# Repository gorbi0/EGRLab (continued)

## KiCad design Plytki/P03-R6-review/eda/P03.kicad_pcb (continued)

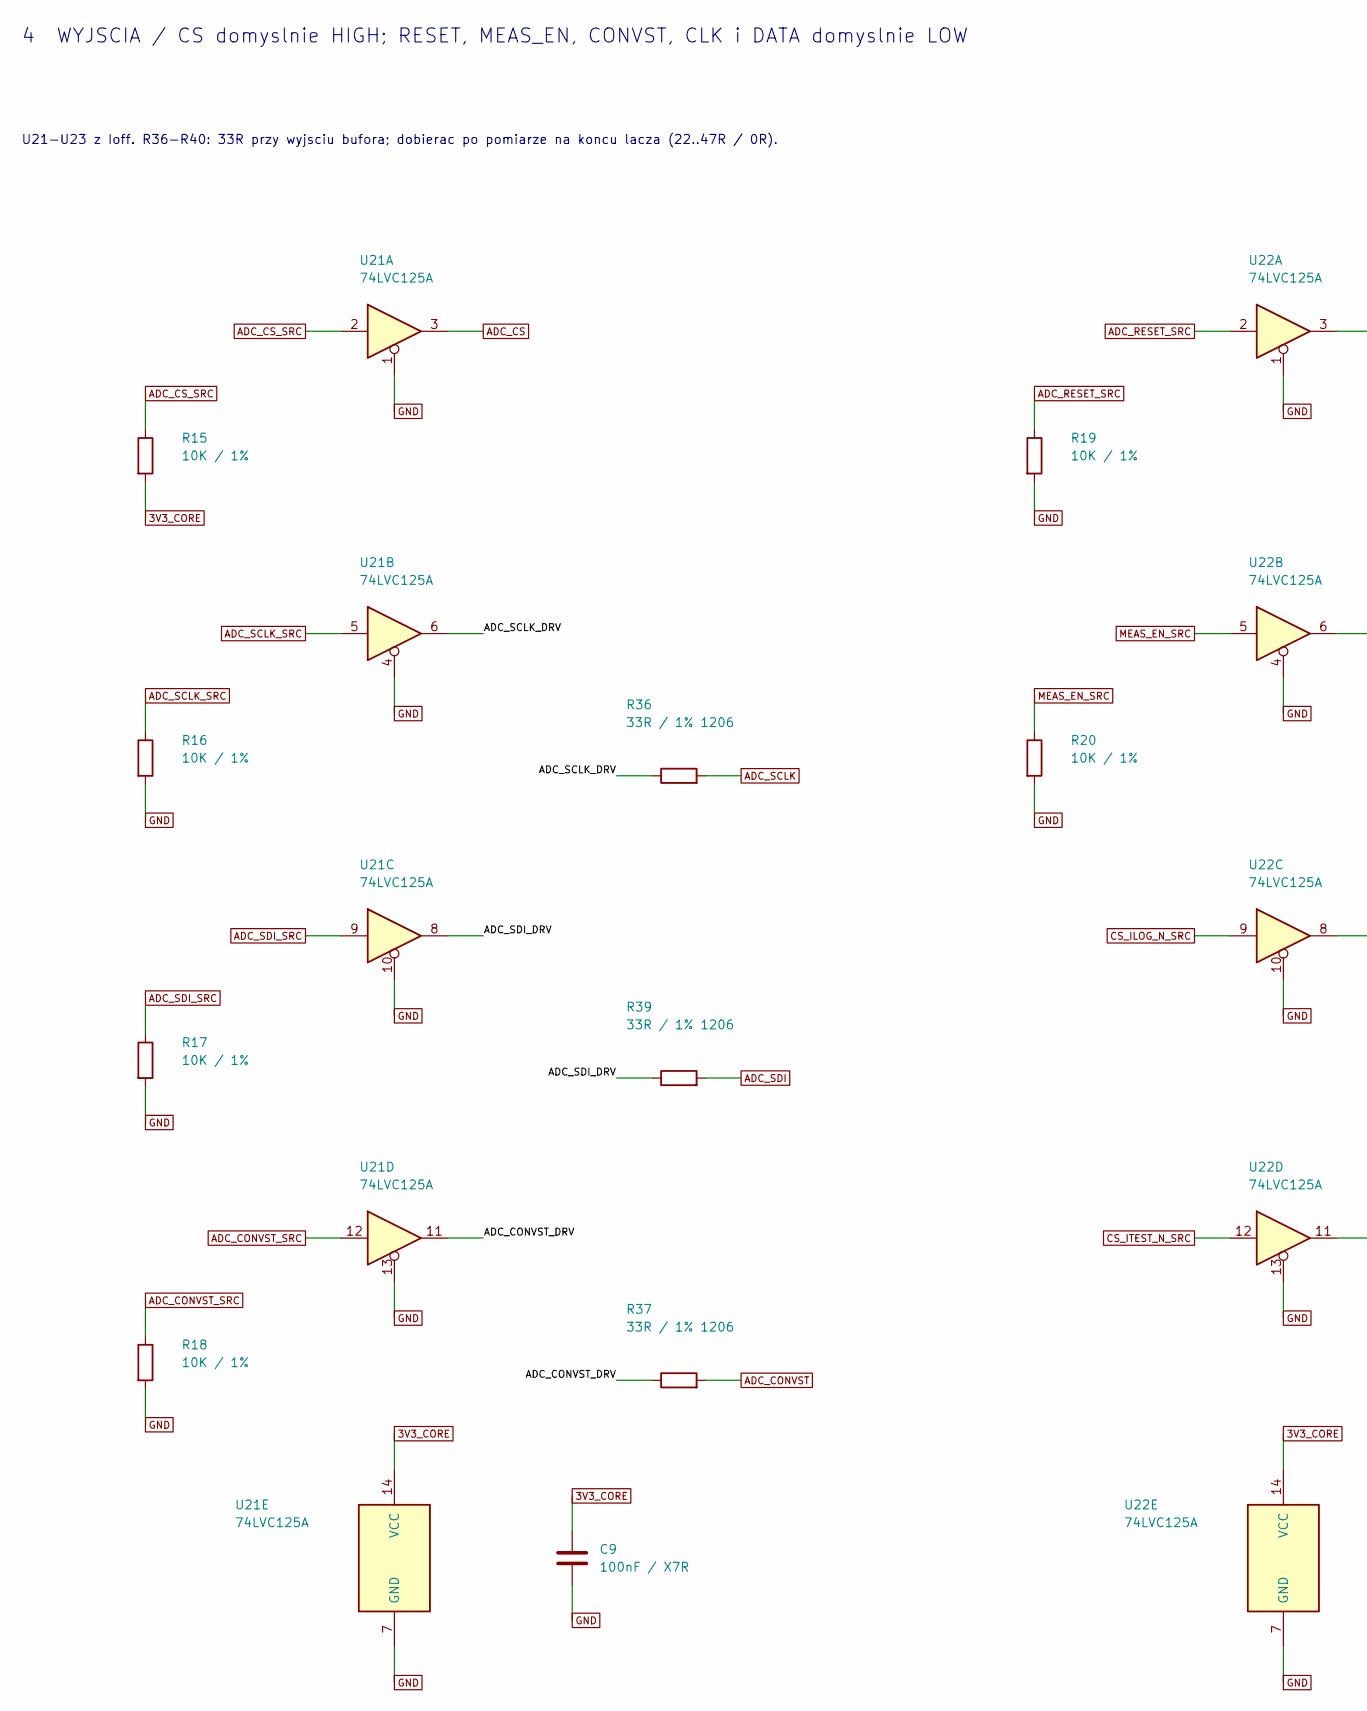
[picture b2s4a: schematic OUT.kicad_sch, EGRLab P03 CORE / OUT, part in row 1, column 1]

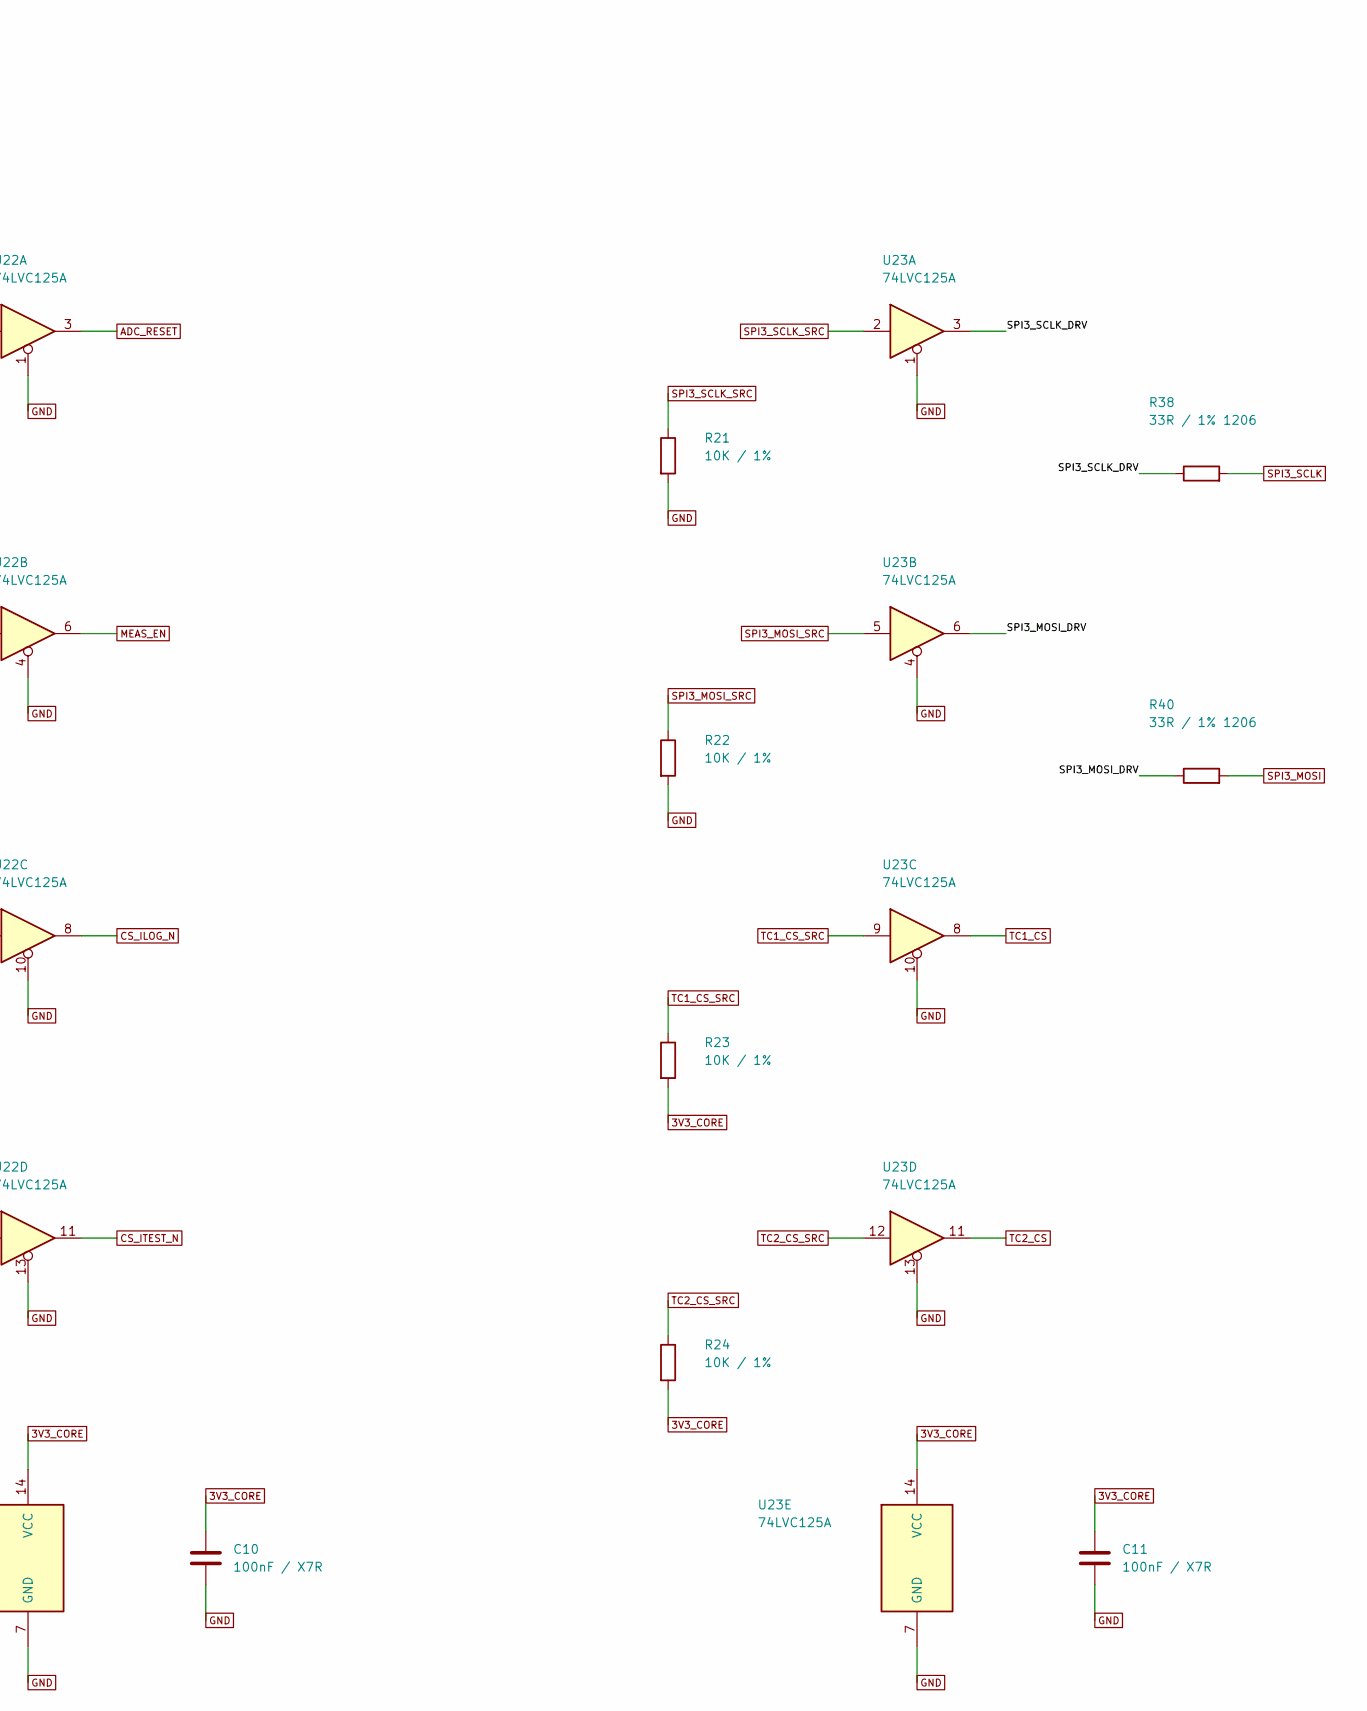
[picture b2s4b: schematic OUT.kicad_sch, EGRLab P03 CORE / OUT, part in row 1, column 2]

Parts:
C9, C10, C11: 100nF / X7R; C_Vishay_K15_H5_P5; MPN K104K15X7RF5TH5
R15, R16, R17, R18, R19, R20, R21, R22, R23, R24: 10K / 1%; R_Axial_DIN0207_L6.3mm_D2.5mm_P5.08mm_Vertical; MPN MF0207FTE-10K
R36, R37, R38, R39, R40: 33R / 1% 1206; R_1206_3216Metric_Pad1.30x1.75mm_HandSolder; MPN RC1206FR-0733RL
U21, U22, U23: 74LVC125A; SOIC-14_3.9x8.7mm_P1.27mm; MPN 74LVC125AD,118 (Nexperia)

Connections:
3V3_CORE: C9.1, C10.1, C11.1, R15.2, R23.2, R24.2, U21.14 (VCC), U22.14 (VCC), U23.14 (VCC); also elsewhere on the board
/OUT/ADC_CONVST_DRV: R37.1, U21.11
/OUT/ADC_SCLK_DRV: R36.1, U21.6
/OUT/ADC_SDI_DRV: R39.1, U21.8
/OUT/SPI3_MOSI_DRV: R40.1, U23.6
/OUT/SPI3_SCLK_DRV: R38.1, U23.3
ADC_CONVST: R37.2; also elsewhere on the board
ADC_CONVST_SRC: R18.1, U21.12; also elsewhere on the board
ADC_CS: U21.3; also elsewhere on the board
ADC_CS_SRC: R15.1, U21.2; also elsewhere on the board
ADC_RESET_SRC: R19.1, U22.2; also elsewhere on the board
ADC_SCLK: R36.2; also elsewhere on the board
ADC_SCLK_SRC: R16.1, U21.5; also elsewhere on the board
ADC_SDI: R39.2; also elsewhere on the board
ADC_SDI_SRC: R17.1, U21.9; also elsewhere on the board
CS_ILOG_N: U22.8; also elsewhere on the board
CS_ILOG_N_SRC: U22.9; also elsewhere on the board
CS_ITEST_N: U22.11; also elsewhere on the board
CS_ITEST_N_SRC: U22.12; also elsewhere on the board
MEAS_EN: U22.6; also elsewhere on the board
MEAS_EN_SRC: R20.1, U22.5; also elsewhere on the board
SPI3_MOSI: R40.2; also elsewhere on the board
SPI3_MOSI_SRC: R22.1, U23.5; also elsewhere on the board
SPI3_SCLK: R38.2; also elsewhere on the board
SPI3_SCLK_SRC: R21.1, U23.2; also elsewhere on the board
TC1_CS: U23.8; also elsewhere on the board
TC1_CS_SRC: R23.1, U23.9; also elsewhere on the board
TC2_CS: U23.11; also elsewhere on the board
TC2_CS_SRC: R24.1, U23.12; also elsewhere on the board

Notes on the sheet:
4 WYJSCIA / CS domyslnie HIGH; RESET, MEAS_EN, CONVST, CLK i DATA domyslnie LOW
U21-U23 z Ioff. R36-R40: 33R przy wyjsciu bufora; dobierac po pomiarze na koncu lacza (22..47R / 0R).

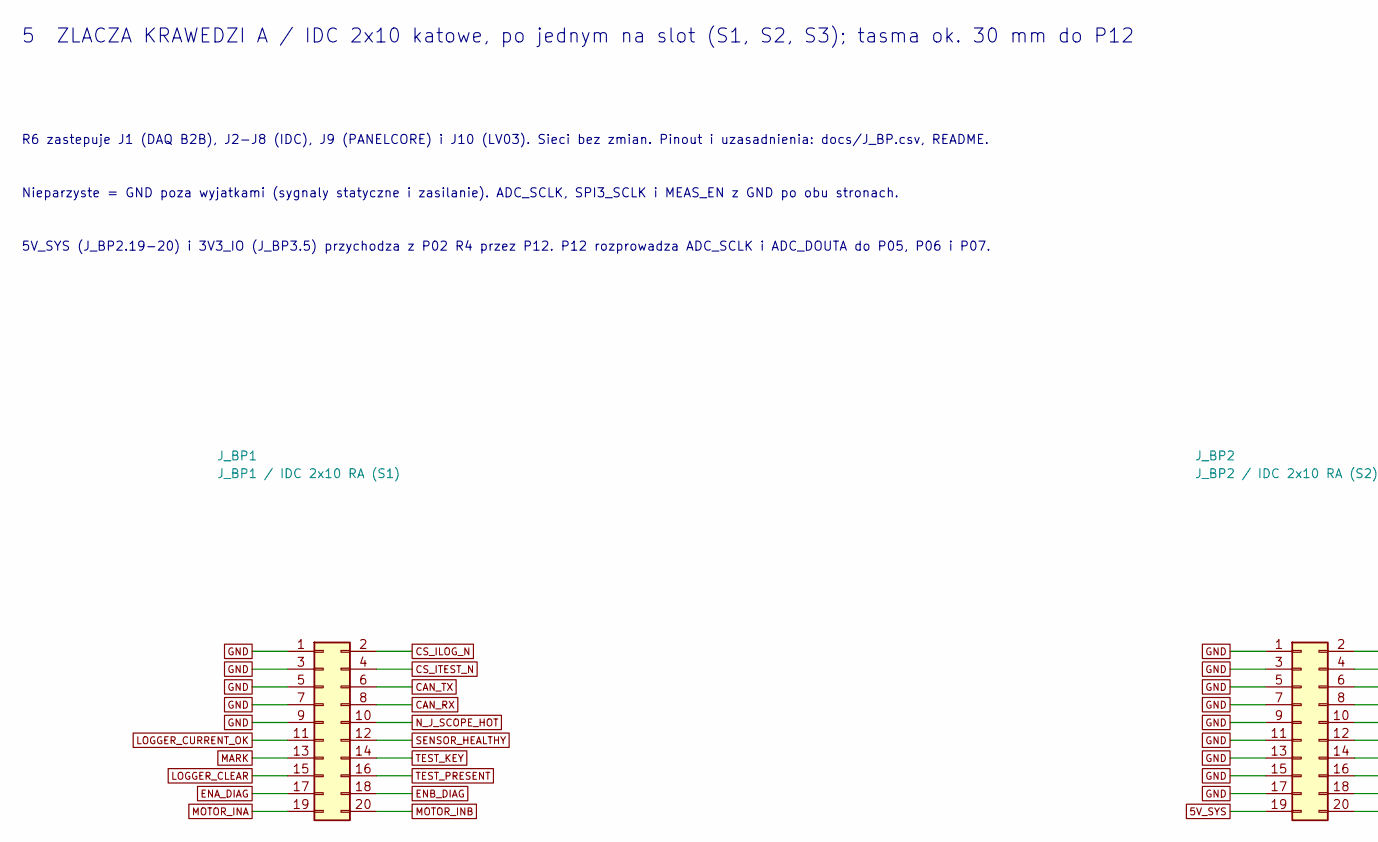
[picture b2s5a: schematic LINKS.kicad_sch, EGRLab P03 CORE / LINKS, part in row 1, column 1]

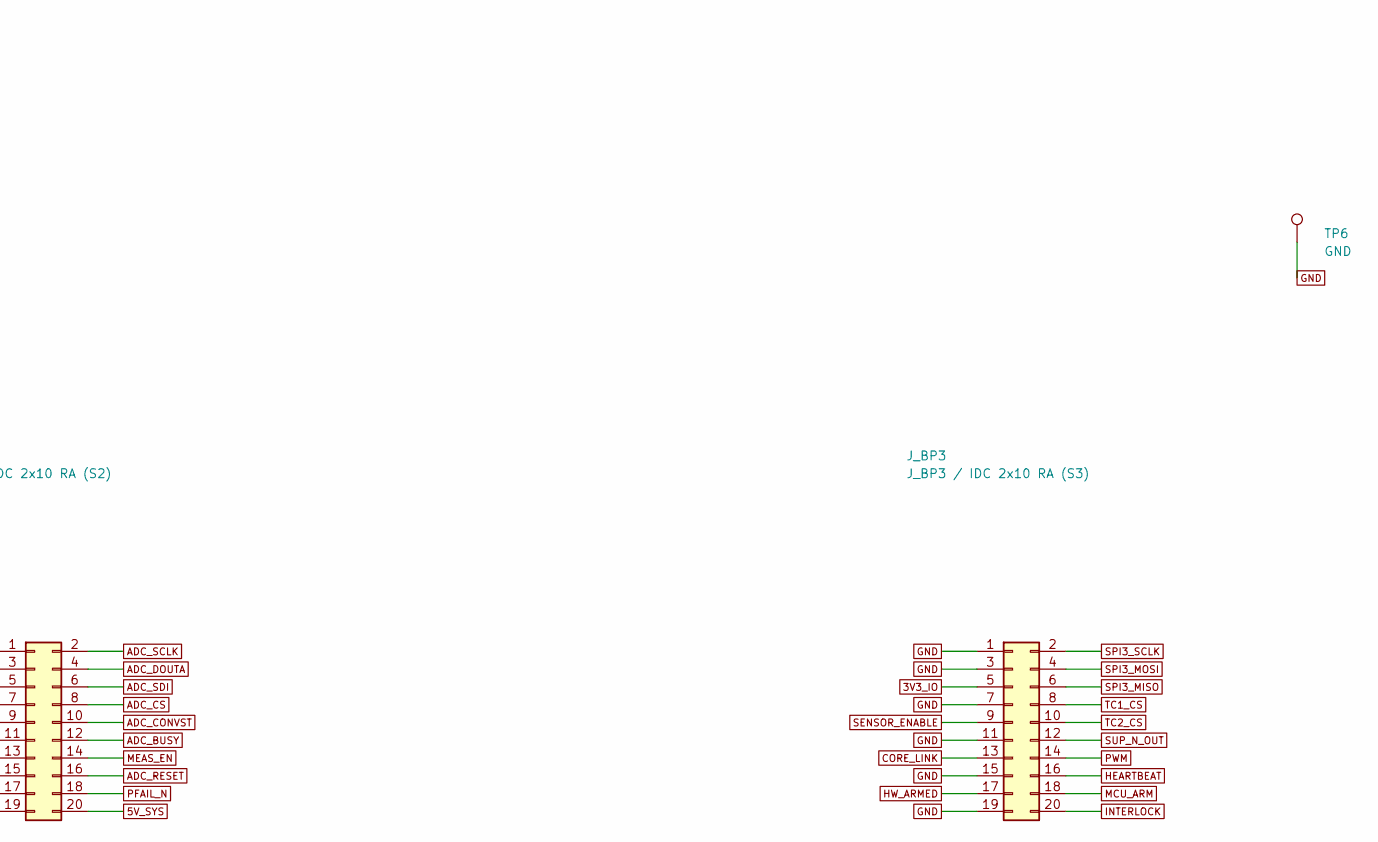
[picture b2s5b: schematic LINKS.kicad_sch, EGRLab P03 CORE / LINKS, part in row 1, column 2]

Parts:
J_BP1: J_BP1 / IDC 2x10 RA (S1); IDC-Header_2x10_P2.54mm_Horizontal; MPN IDC box header 2x10, 2.54 mm, right ang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
J_BP2: J_BP2 / IDC 2x10 RA (S2); IDC-Header_2x10_P2.54mm_Horizontal; MPN IDC box header 2x10, 2.54 mm, right ang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
J_BP3: J_BP3 / IDC 2x10 RA (S3); IDC-Header_2x10_P2.54mm_Horizontal; MPN IDC box header 2x10, 2.54 mm, right ang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
TP6: GND; TestPad_1; MPN PCB test pad

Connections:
3V3_IO: J_BP3.5; also elsewhere on the board
ADC_BUSY: J_BP2.12; also elsewhere on the board
ADC_CONVST: J_BP2.10; also elsewhere on the board
ADC_CS: J_BP2.8; also elsewhere on the board
ADC_DOUTA: J_BP2.4; also elsewhere on the board
ADC_SCLK: J_BP2.2; also elsewhere on the board
ADC_SDI: J_BP2.6; also elsewhere on the board
CAN_RX: J_BP1.8; also elsewhere on the board
CAN_TX: J_BP1.6; also elsewhere on the board
CORE_LINK: J_BP3.13; also elsewhere on the board
CS_ILOG_N: J_BP1.2; also elsewhere on the board
CS_ITEST_N: J_BP1.4; also elsewhere on the board
ENA_DIAG: J_BP1.17; also elsewhere on the board
ENB_DIAG: J_BP1.18; also elsewhere on the board
HEARTBEAT: J_BP3.16; also elsewhere on the board
HW_ARMED: J_BP3.17; also elsewhere on the board
INTERLOCK: J_BP3.20; also elsewhere on the board
LOGGER_CLEAR: J_BP1.15; also elsewhere on the board
MARK: J_BP1.13; also elsewhere on the board
MCU_ARM: J_BP3.18; also elsewhere on the board
MEAS_EN: J_BP2.14; also elsewhere on the board
MOTOR_INA: J_BP1.19; also elsewhere on the board
MOTOR_INB: J_BP1.20; also elsewhere on the board
N_J_SCOPE_HOT: J_BP1.10; also elsewhere on the board
PWM: J_BP3.14; also elsewhere on the board
SENSOR_ENABLE: J_BP3.9; also elsewhere on the board
SENSOR_HEALTHY: J_BP1.12; also elsewhere on the board
SPI3_MISO: J_BP3.6; also elsewhere on the board
SPI3_MOSI: J_BP3.4; also elsewhere on the board
SPI3_SCLK: J_BP3.2; also elsewhere on the board
SUP_N_OUT: J_BP3.12; also elsewhere on the board
TC1_CS: J_BP3.8; also elsewhere on the board
TC2_CS: J_BP3.10; also elsewhere on the board
TEST_KEY: J_BP1.14; also elsewhere on the board
TEST_PRESENT: J_BP1.16; also elsewhere on the board

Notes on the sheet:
5 ZLACZA KRAWEDZI A / IDC 2x10 katowe, po jednym na slot (S1, S2, S3); tasma ok. 30 mm do P12
R6 zastepuje J1 (DAQ B2B), J2-J8 (IDC), J9 (PANELCORE) i J10 (LV03). Sieci bez zmian. Pinout i uzasadnienia: docs/J_BP.csv, README.
Nieparzyste = GND poza wyjatkami (sygnaly statyczne i zasilanie). ADC_SCLK, SPI3_SCLK i MEAS_EN z GND po obu stronach.
5V_SYS (J_BP2.19-20) i 3V3_IO (J_BP3.5) przychodza z P02 R4 przez P12. P12 rozprowadza ADC_SCLK i ADC_DOUTA do P05, P06 i P07.

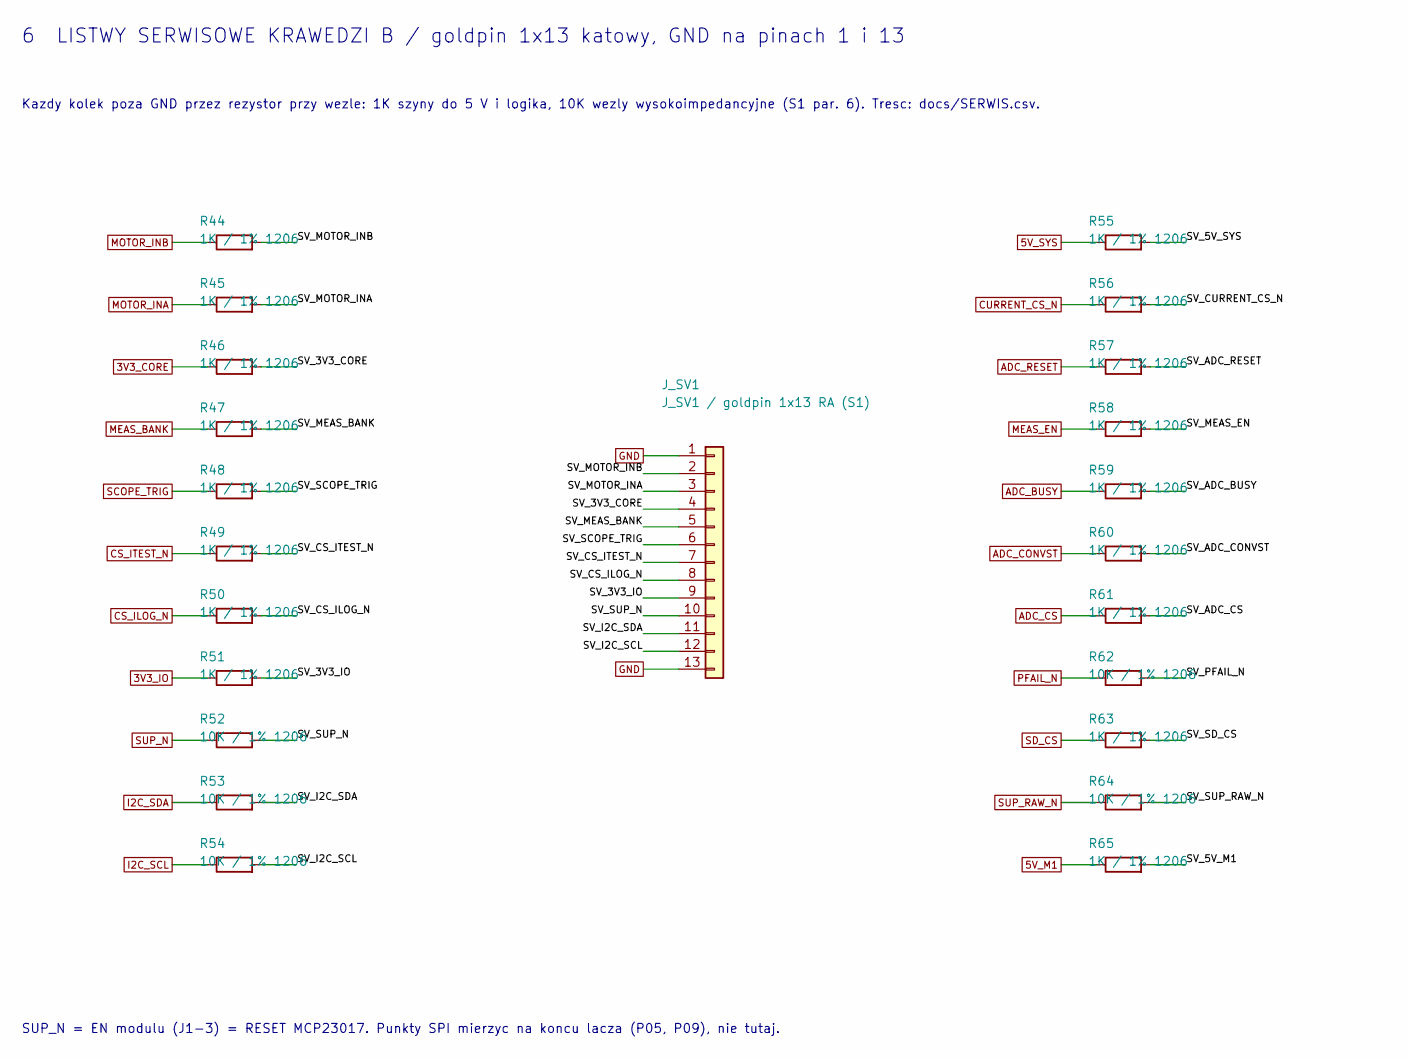
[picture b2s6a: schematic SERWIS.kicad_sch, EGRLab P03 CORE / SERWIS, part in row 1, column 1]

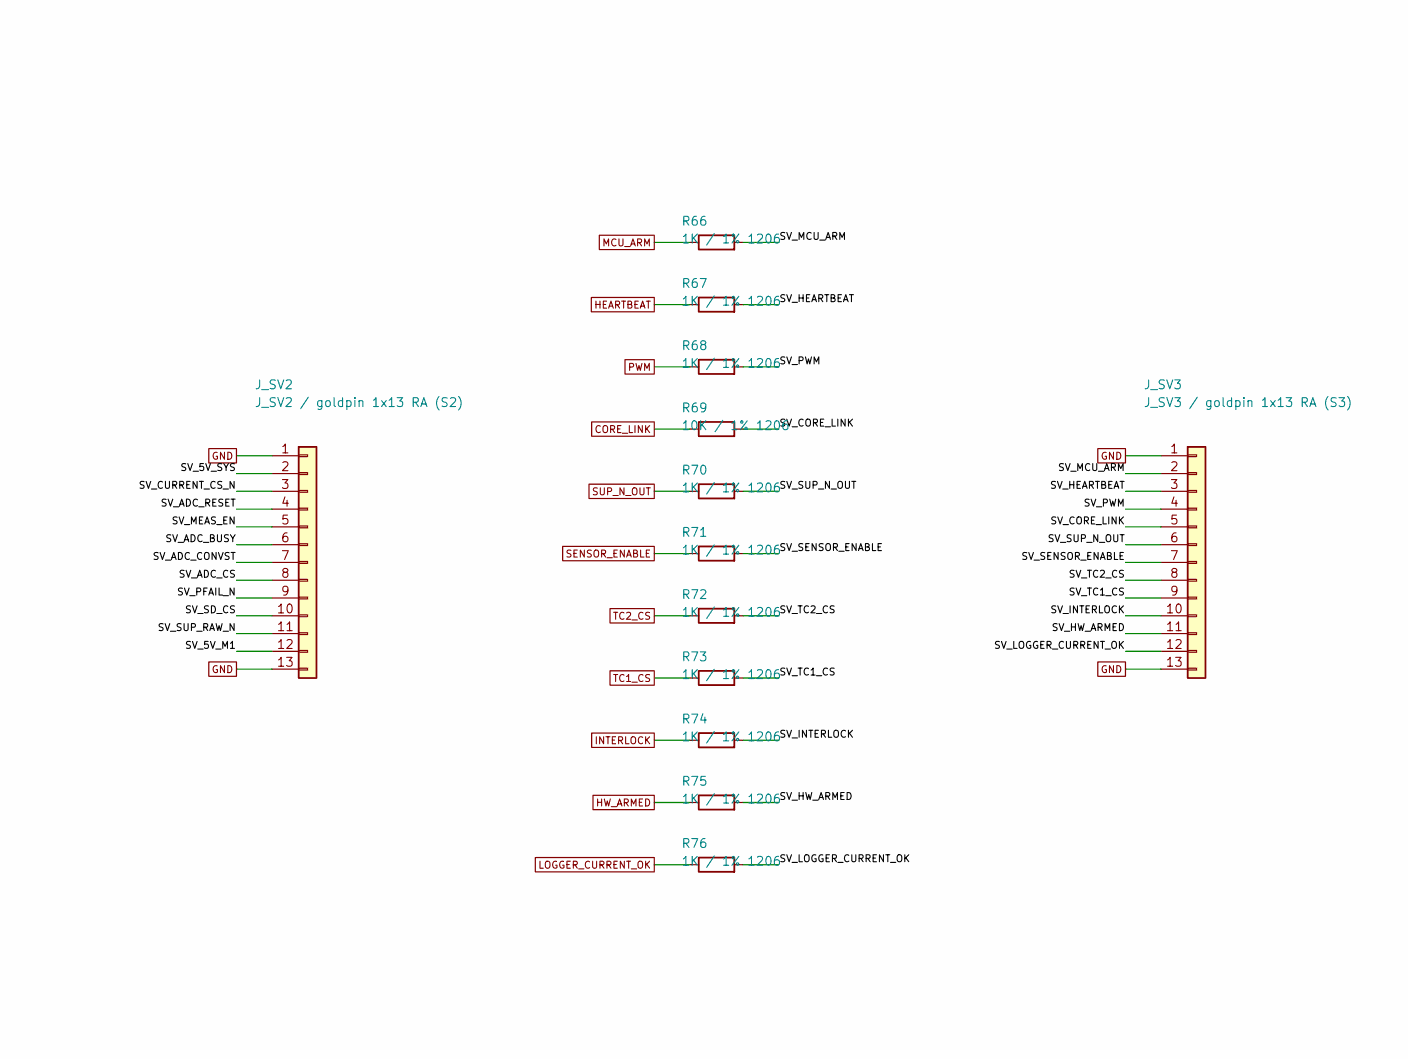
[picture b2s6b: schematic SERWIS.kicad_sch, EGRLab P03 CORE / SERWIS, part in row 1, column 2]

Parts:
J_SV1: J_SV1 / goldpin 1x13 RA (S1); PinHeader_1x13_P2.54mm_Horizontal; MPN Pin header 1x13, 2.54 mm, right angle, 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
J_SV2: J_SV2 / goldpin 1x13 RA (S2); PinHeader_1x13_P2.54mm_Horizontal; MPN Pin header 1x13, 2.54 mm, right angle, 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
J_SV3: J_SV3 / goldpin 1x13 RA (S3); PinHeader_1x13_P2.54mm_Horizontal; MPN Pin header 1x13, 2.54 mm, right angle, 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
R44, R45, R46, R47, R48, R49, R50, R51, R55, R56, R57, R58, R59, R60, R61, R63, R65, R66, R67, R68, R70, R71, R72, R73, R74, R75, R76: 1K / 1% 1206; R_1206_3216Metric_Pad1.30x1.75mm_HandSolder; MPN RC1206FR-071KL
R52, R53, R54, R62, R64, R69: 10K / 1% 1206; R_1206_3216Metric_Pad1.30x1.75mm_HandSolder; MPN RC1206FR-0710KL

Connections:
3V3_CORE: R46.1; also elsewhere on the board
3V3_IO: R51.1; also elsewhere on the board
5V_M1: R65.1; also elsewhere on the board
/SERWIS/SV_3V3_CORE: J_SV1.4, R46.2
/SERWIS/SV_3V3_IO: J_SV1.9, R51.2
/SERWIS/SV_5V_M1: J_SV2.12, R65.2
/SERWIS/SV_5V_SYS: J_SV2.2, R55.2
/SERWIS/SV_ADC_BUSY: J_SV2.6, R59.2
/SERWIS/SV_ADC_CONVST: J_SV2.7, R60.2
/SERWIS/SV_ADC_CS: J_SV2.8, R61.2
/SERWIS/SV_ADC_RESET: J_SV2.4, R57.2
/SERWIS/SV_CORE_LINK: J_SV3.5, R69.2
/SERWIS/SV_CS_ILOG_N: J_SV1.8, R50.2
/SERWIS/SV_CS_ITEST_N: J_SV1.7, R49.2
/SERWIS/SV_CURRENT_CS_N: J_SV2.3, R56.2
/SERWIS/SV_HEARTBEAT: J_SV3.3, R67.2
/SERWIS/SV_HW_ARMED: J_SV3.11, R75.2
/SERWIS/SV_I2C_SCL: J_SV1.12, R54.2
/SERWIS/SV_I2C_SDA: J_SV1.11, R53.2
/SERWIS/SV_INTERLOCK: J_SV3.10, R74.2
/SERWIS/SV_LOGGER_CURRENT_OK: J_SV1.10, R52.2
/SERWIS/SV_MCU_ARM: J_SV3.2, R66.2
/SERWIS/SV_MEAS_BANK: J_SV1.5, R47.2
/SERWIS/SV_MEAS_EN: J_SV2.5, R58.2
/SERWIS/SV_MOTOR_INA: J_SV1.3, R45.2
/SERWIS/SV_MOTOR_INB: J_SV1.2, R44.2
/SERWIS/SV_PFAIL_N: J_SV2.9, R62.2
/SERWIS/SV_PWM: J_SV3.4, R68.2
/SERWIS/SV_SCOPE_TRIG: J_SV1.6, R48.2
/SERWIS/SV_SD_CS: J_SV2.10, R63.2
/SERWIS/SV_SENSOR_ENABLE: J_SV3.7, R71.2
/SERWIS/SV_SUP_N: J_SV3.12, R76.2
/SERWIS/SV_SUP_N_OUT: J_SV3.6, R70.2
/SERWIS/SV_SUP_RAW_N: J_SV2.11, R64.2
/SERWIS/SV_TC1_CS: J_SV3.9, R73.2
/SERWIS/SV_TC2_CS: J_SV3.8, R72.2
ADC_BUSY: R59.1; also elsewhere on the board
ADC_CONVST: R60.1; also elsewhere on the board
ADC_CS: R61.1; also elsewhere on the board
CORE_LINK: R69.1; also elsewhere on the board
CS_ILOG_N: R50.1; also elsewhere on the board
CS_ITEST_N: R49.1; also elsewhere on the board
CURRENT_CS_N: R56.1; also elsewhere on the board
HEARTBEAT: R67.1; also elsewhere on the board
HW_ARMED: R75.1; also elsewhere on the board
I2C_SCL: R54.1; also elsewhere on the board
I2C_SDA: R53.1; also elsewhere on the board
INTERLOCK: R74.1; also elsewhere on the board
MCU_ARM: R66.1; also elsewhere on the board
MEAS_BANK: R47.1; also elsewhere on the board
MEAS_EN: R58.1; also elsewhere on the board
MOTOR_INA: R45.1; also elsewhere on the board
MOTOR_INB: R44.1; also elsewhere on the board
PWM: R68.1; also elsewhere on the board
SCOPE_TRIG: R48.1; also elsewhere on the board
SD_CS: R63.1; also elsewhere on the board
SENSOR_ENABLE: R71.1; also elsewhere on the board
SUP_N_OUT: R70.1; also elsewhere on the board
SUP_RAW_N: R64.1; also elsewhere on the board
TC1_CS: R73.1; also elsewhere on the board
TC2_CS: R72.1; also elsewhere on the board

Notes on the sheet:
6 LISTWY SERWISOWE KRAWEDZI B / goldpin 1x13 katowy, GND na pinach 1 i 13
Kazdy kolek poza GND przez rezystor przy wezle: 1K szyny do 5 V i logika, 10K wezly wysokoimpedancyjne (S1 par. 6). Tresc: docs/SERWIS.csv.
SUP_N = EN modulu (J1-3) = RESET MCP23017. Punkty SPI mierzyc na koncu lacza (P05, P09), nie tutaj.

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
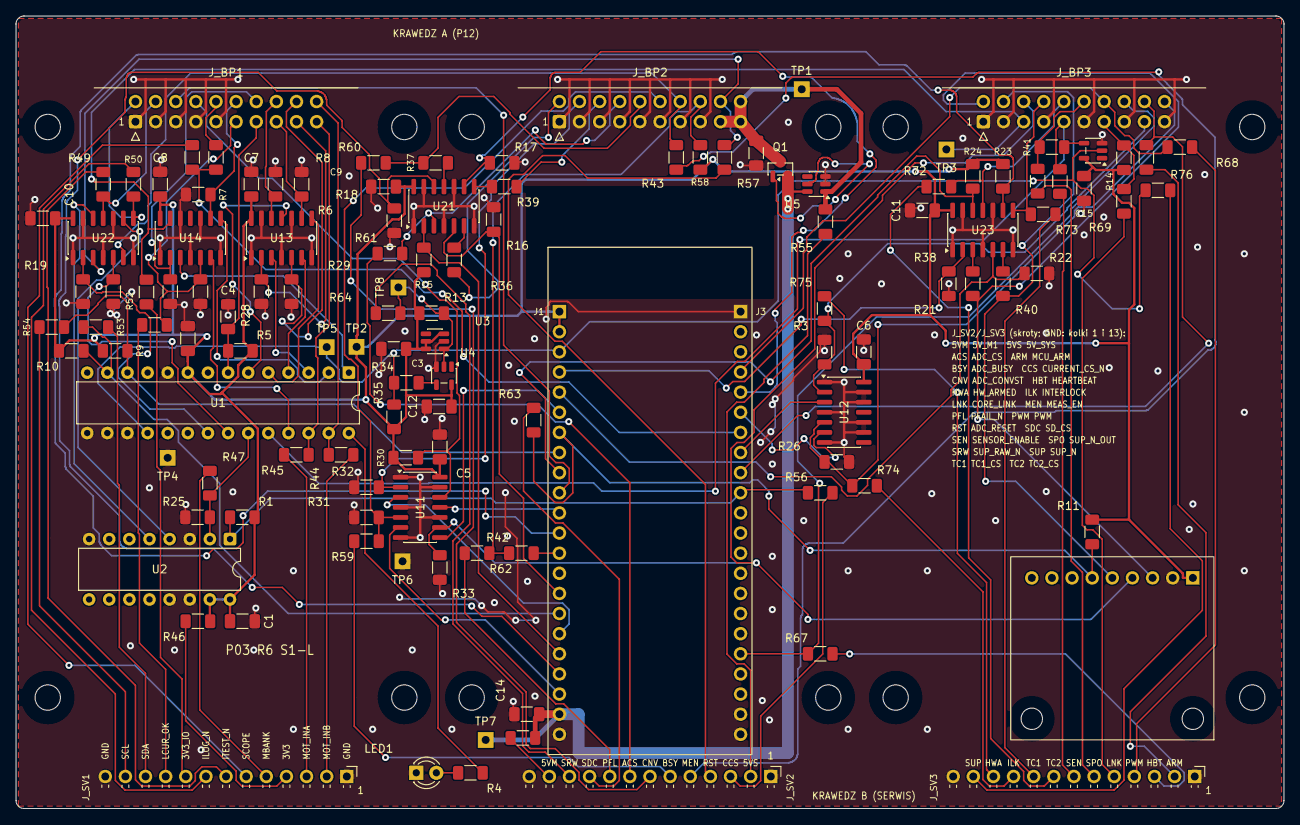
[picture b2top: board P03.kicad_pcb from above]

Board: 2 copper layers, 160.0 x 100.0 mm, 134 parts (0 on the bottom side), 119 nets.

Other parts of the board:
H1, H2, H3, H4, H5, H6, H7, H8, H9, H10, H11, H12: M3 NPTH
